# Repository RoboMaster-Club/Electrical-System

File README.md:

# Robomaster Electrical System Repo
Welcome to Purdue Robomaster Club's Electrical System Repository Created by Chengming Zhang. This repository contain everything from PCB design, Design Notebook (In sub-folder's ReadMe.md), and softwares. 

If you are not familier with Robomaster, or Purdue's Robomaster Team, please refer to [Our Website](https://www.PurdueRM.com "Purdue Robomaster") or check out this video covered by **The Verge**.

<br><br>

<iframe width="560" height="315" src="https://www.youtube.com/embed/ECr4zgK6cPA" frameborder="0" allow="accelerometer; autoplay; encrypted-media; gyroscope; picture-in-picture" allowfullscreen></iframe>

## Team Structure

**Electrical Team Lead**: Chengming Zhang ` @cmz97` 

**Active Member:**

Henry Silva ` @Lazloian` 

Dansen Wang ` @cmz97` 

MingCheng Li ` @blaticslm` 

Ben Mirvish ` @bmivish` 

## Project Structure

📣**For detail design notebook, pls visit the coresponding directory**📣

▶️ Work in-Progress

🔜 Future Project

🉑 Completed Project

🔂 New Iteration

‼️ Need Documentation

⚠️ Ship Blocker

🚮 Abanded Project

<br><br>

The image bellow is our latest **Electrical System Diagram** which lays out all the connection between our subsystems.

## Power Electronics

### Super Capacitor Bank ‼️ ▶️ ⚠️

 `Made by @bmirvish @blaticslm`

Due to the competition rule, the robot chassis, which consists of four DJI 3508 geared brushless motor, can not draw more than 240W of power at any given time. To overcome this limitation, we designed our custom made supercapacitor bank as a buffer that provides instantaneous power to our robot on demand. **This Capacitor Bank only consist of voltage banlancing circuit, ADC, and the Super Capacitor Unit.** Since this is a passive electrical unit, there is no firmware.

> Plan for your PCB, Electrical Parameter and Mechinical Parameters like dimentions in your own folder‼️

> * PCB Design  @#todo‼️
> * CAD Design Enclosure @#google drive link‼️

<br>

### Super Capacitor Charger (STM32) ‼️ 🔜 ⚠️ 🔂

`Made by @cmz97`

Since Capacitor is a short circuit when not charged, we need to design a consitance current charger to avoid damage of the battery and capacitor. Chengming Selected to use a H bridge Configuration to create a custon buck convertor using STM32F334. Currently, the Super Capacitor Charger can takes any voltage between 5v - 50v and convert it to 1v - 40v. The maxium output current is 10A. The PCB has a dimension of 2.599 in x 2.487 in and four layer. 

<br>

PCB Design @[SuperCapacitor-v2.0](https://github.com/RoboMaster-Club/Electrical-System/tree/master/SuperCapacitor-v2.0)

Firmware @[SuperCapacitor-v2.0](https://github.com/RoboMaster-Club/Electrical-System/tree/master/SuperCapacitor-v2.0)

<br>

### Power Distribution Boards 🉑

Power Distribution Board is used to distribute electrical current in different voltage across the robot. Currently the Robot takes the following voltage level. 

> **24 Volt** for Robot controller, Any motor

> **12 Volt** for Jetson TX 2, Transparent OLED

> **5 Volt** for Gimbal Electrical Controller Board (ATMEGA), Electrical System Controller(ESP32)

> **3.3 Volt** for all the embedded chip, STM32F4, ESP32, ATMEGA

> **1.5 Volt** for Ammo remaining detection circuit

For a more accurate and compelete report on voltage and current usage of our robot, pls refer to [Power Distribution Board Design Log](https://github.com/RoboMaster-Club/Electrical-System/blob/master/Power-Distribution-Board-V3.0/README.md)

The newst power distribution board is divided into three seperated board:

<br>

### Chassis Power Distribution Board

`Made by @cmz97`

This board provides all the power delivery on the robot chassis, which consist of four DJI M3508 Motor. It also has a 3.3v relay on board that selection output from either the super capacitor bank or the battery directorly. This switching action can be controlled by software via a logic high, which is passed through a opto-isolator  for signal isolation. In case of emergency, such as super capacitor failure, one can flip a by-pass switch that disable all software input, and force the circuit to take battery input only. 

<br><br>

The software switch is controlled by the Electrical System Controller (STM32/ESP32) that switch the output dynamically according to the current power usage. In seniorio such as low votage on super capacitor, Electrical System Controller can select battery input to avoid damage to the supercapacitor, and left it for charging. 

[Chassis Power Distribution Board  Repository for Detail Info](https://github.com/RoboMaster-Club/Electrical-System/tree/master/Power-Distribution-Board-V3.0/Chassis%20Power%20Distribution%20Board)‼️

<br>

### Slip-Ring Power Distribution Board

`Made by @cmz97`

This board provides power to the Pitch Motor for the gimbal system, as well as power for Electrical System Controller. The board also provides pre-organization of the wires that go up through the slip-ring. Slipring is used in the robot due to mechanical constraints, where the robot's gimbal needs to rotate continuously. Since there are only 24 wires passess through the slipring used in our standard robot, with each of the wire capable of carring 2A of maxium continouse current, proper signal allocation need to be conducted. <br><br>

We concluded the following wiring asssignment:

| Signal Name     | 8A Power | 8A GND | 4A Power | 4A GND | Motor CAN H | Motor CAN L | REF_TX | REF_RX | GPIO | ESP32_TX | Referee System | Ammo Boost |
| --------------- | -------- | ------ | -------- | ------ | ----------- | ----------- | ------ | ------ | ---- | -------- | -------------- | ---------- |
| # of Wire       | 4        | 4      | 2        | 2      | 1           | 1           | 1      | 1      | 1    | 1        | 4              | 2          |
| Max Current (A) | 8        | 8      | 4        | 4      | 2           | 2           | 2      | 2      | 2    | 2        | 2              | 2          |

<br><br>

[SlipRing Distribution Board Repository for Detail Info](https://github.com/RoboMaster-Club/Electrical-System/tree/master/Power-Distribution-Board-V3.0/SlipRing%20Distribution%20Board)

<br>

### Gimbal Power Distribution Board

`Made by @cmz97`

This board provides power to the STM32 Robot controller, JetsonTX2, Yall Motor, Flywheel, ammo motor, as well as the Gimbal Electrical System Controller. On board this board, there are two MP1584EN buck convertor that converts 24v from the battery to 12v for Tx2 and 5v for the Gimbal Electrical System Controller.

[Robomater Gimbal Power Distribution Board Repository for Detail Info](https://github.com/RoboMaster-Club/Electrical-System/tree/master/Power-Distribution-Board-V3.0/Robomater%20Gimbal%20Power%20Distribution%20Board)

<br>
<br>

## Embedded Systems

### Electrical System Controller (STM32) ‼️🔂

* PCB Design `Made by @cmz97`

* Firmware `Made by @William-An`

<br>

### Remote Electrical System Monitor ‼️🔜

`Made by @cmz97`

<br>

### Gimbal Electrical System Controller (ATMEGA) 🔂 ▶️‼️

 `Made by @Lazloian`

  System Controller uses a transparent OLED in front of the driver's camera to display information to the driver. Board recieves info from ammo detector and tof sensors

  HUD Info

  * Lines on the sides indicate walls that are close to the robot

  * Cross hairs in the center of the screen indicate low ammo in the hopper

<br>

### Low Ammo Detection ‼️🔜

 `Made by @Lazloian`

<br>

### Robot Controller (STM32) ‼️

<br>

### Computer Vision System (Jetson TX 2)‼️

<br>

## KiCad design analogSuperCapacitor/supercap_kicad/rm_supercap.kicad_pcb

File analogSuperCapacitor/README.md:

# Passive Super-Capacitor Design
In order to be able to used more than 80W of power at any instatianious time, a super-capacitor bank is needed to "smooth" the power draw.

## Usage

First download or clone `Passive Super-Capacitor Design`:

Open Kicad and open the Kicad project file.
```sh
rm_supercap.pro
```

Once selected the project should be loaded and ready to view or edit!

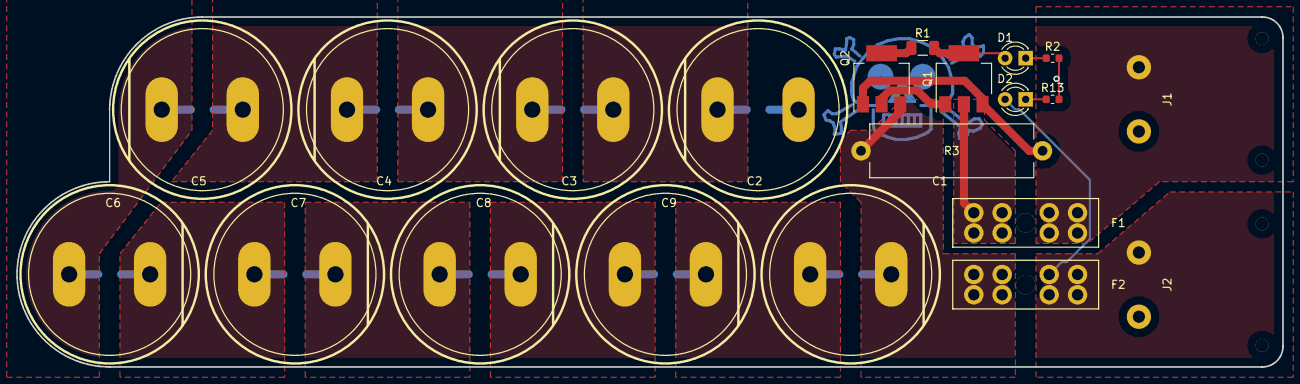
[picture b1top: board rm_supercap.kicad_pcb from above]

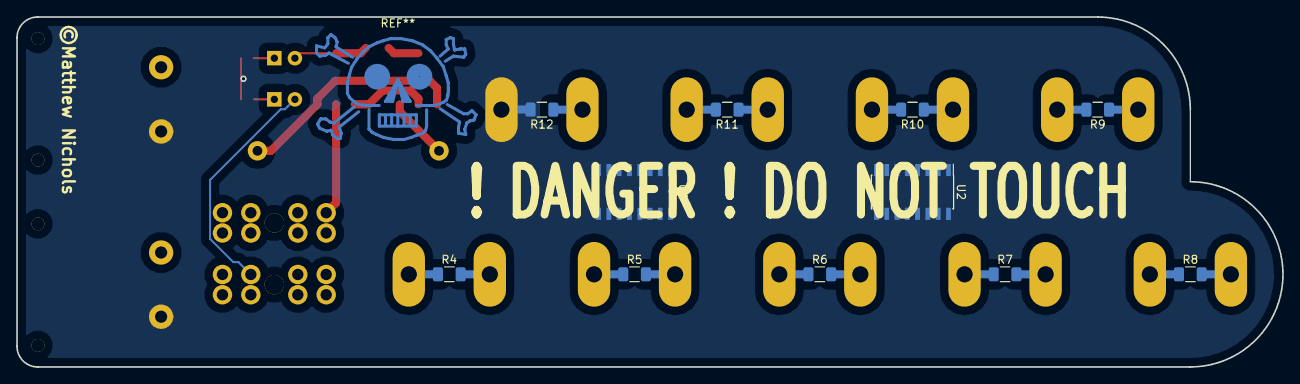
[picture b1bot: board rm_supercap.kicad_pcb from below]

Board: 2 copper layers, 156.2 x 43.2 mm, 32 parts (11 on the bottom side), 17 nets.

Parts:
C1, C2, C3, C4, C5, C6, C7, C8, C9: 100F; CAP_10mm
D1, D2: LED; LED_D3.0mm
F1: Fuse 5A; fuse_holder
F2: Fuse 40A; fuse_holder
J1, J2: Conn_01x02_Female; H10710
Q1, Q2: Q_NPN_BCE; SOT-223-3_TabPin2
R1: 100; R_1206_3216Metric
R2, R13: 10K; R_0603_1608Metric
R3: 0.22; R_Axial_Power_L20.0mm_W6.4mm_P22.40mm
R4, R5, R6, R7, R8, R9, R10, R11, R12: 100K; R_1206_3216Metric
U1, U2: ALD810027; SOIC-16_3.9x9.9mm_P1.27mm

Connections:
GND: C9.2, J1.2, J2.2, R2.2, R12.2, R13.2
unnamed: C1.1, F2.2, Q2.3, R3.1, R4.1, U1.11
unnamed: C1.2, C2.1, R4.2, R5.1, U1.6, U1.7, U1.9
unnamed: C2.2, C3.1, R5.2, R6.1, U1.8
unnamed: C3.2, C4.1, R6.2, R7.1, U2.2, U2.3
unnamed: C4.2, C5.1, R7.2, R8.1, U2.4, U2.14, U2.15
unnamed: C5.2, C6.1, R8.2, R9.1, U2.11
unnamed: C6.2, C7.1, R9.2, R10.1, U2.6, U2.7, U2.9
unnamed: C7.2, C8.1, R10.2, R11.1, U2.8
unnamed: C8.2, C9.1, R11.2, R12.1
unnamed: D1.1, R2.1
unnamed: D1.2, F1.1, Q1.2, R1.2
unnamed: D2.1, R13.1
unnamed: D2.2, F2.1, J2.1
unnamed: F1.2, J1.1
unnamed: Q1.1, Q2.2, R1.1
unnamed: Q1.3, Q2.1, R3.2

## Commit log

2019-01-28 Create Voltage Regulator Code
2019-02-02 Update project structure && README file
2019-02-02 Update folder structure and README
2019-02-02 initial upload
2019-02-08 Temperature Sensor
    This is the temperature sensor with the measured results displayed on LCD.
2019-02-08 Add files via upload
    This is the code for testing
2019-02-09 added img
2019-02-16 Combine Voltage Regulater2
2019-02-16 Description for volRegulator
2019-02-16 TempSensor Guide
2019-02-22 schematic_2/2019
    The voltage regulator needs to be changed.
    LCD and I2C need to be added
2019-02-23 Sample code from Adafruit
2019-02-28 Electrical System Diagram
2019-03-02 Create server
2019-03-02 Add files via upload
    the voltage regulator will be changed later.
2019-03-08 This is PCB design for buck converter circuit.
2019-03-16 include 3 files in global
2019-03-23 Create Combined_UART.ino
    From Arduino board to HUD system. Displaying Vbat, Vcap, Temp..
2019-03-23 Create Web Browser
2019-03-25 Unzip buck converter design
2019-03-25 Remove buck circuit zip file from github
2019-03-30 working code
2019-03-30 platformIO project
2019-03-30 index on charBranch: e3ba9fe platformIO project
2019-04-02 Finished basic http server, websocket handler, basic web interface
2019-04-10 Set websocket to broad every connected device
2019-04-10 Reorganize project folder
2019-04-10 Move all content to embeddedSystem folder
2019-04-11 Test oledmonitor lib
2019-04-13 Finish sd logger wrapper class and python decoder
2019-04-13 Integrate logger and oled to main executive
2019-04-14 Integrate PDP measurement
2019-04-14 Remove files
2019-04-27 Rearrange development structure
2019-04-27 Rearrange project folder
2019-05-04 Add files via upload
    my shit
2019-05-20 Add time of flight sensor manager
2019-05-21 Add startup sound
2019-05-21 Update web interface; finish digital control via MCP23008
2019-07-18 added some circuit and updated old ones
2019-09-14 README.md
    Project progress update
2019-09-14 Create README.md
    Constant updating the project progress
2019-09-14 update from Kevin's Local Files
2019-09-14 Added Fun.txt
2019-09-14 removed fun.txt
2019-09-14 rename a bunch of stuff
2019-09-28 changed electrical diagram
2019-11-10 updated all power distribution board
2019-11-10 re-orginize our folder structure
2019-11-10 added changes since repo changes
2019-11-10 changed new system diagram
2019-11-10 readme updated
2019-11-11 readme changes
2019-11-11 added gitignore for bash script
2019-11-11 updated the readme
2019-11-14 added changes that were left behind
2019-12-07 Ammo Board V2
2019-12-31 ready
2020-01-06 added project
2020-01-08 test board update
2020-01-25 OLED board update
2020-01-26 added notes
2020-02-11 fixed mistake by ben, approved for manufacturing
2020-03-01 Kevin fixed the v4 controller board! Please review it carefully
2020-03-05 fixed batt power and usb-c power conflict in the Draft Folder
2020-03-05 deleted the temp file
2020-03-06 Thursday Meeting changes to the brd, waiting for final submit
2020-03-07 almost done kevin
2020-03-07 Add files via upload
    Current incomplete parts list for new board
2020-03-07 Updated Schematic
2020-03-08 final -kevin
2020-03-08 3d file uploaded
2020-03-08 added multiplexer board
2020-03-08 Create readme.md
    Siyu created the first version of readme file
2020-03-10 Update readme.md
    Siyu updates I2C Address

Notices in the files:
analogSuperCapacitor/supercap_kicad/rm_supercap.kicad_pcb:
©Matthew Nichols
